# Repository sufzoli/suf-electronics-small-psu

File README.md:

# suf-electronics-small-psu
Collection of my small power supply circuits

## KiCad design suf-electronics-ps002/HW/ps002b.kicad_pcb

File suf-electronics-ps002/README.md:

suf-electronics-ps002
=====================

+/-12V 100mA USB Power Supply

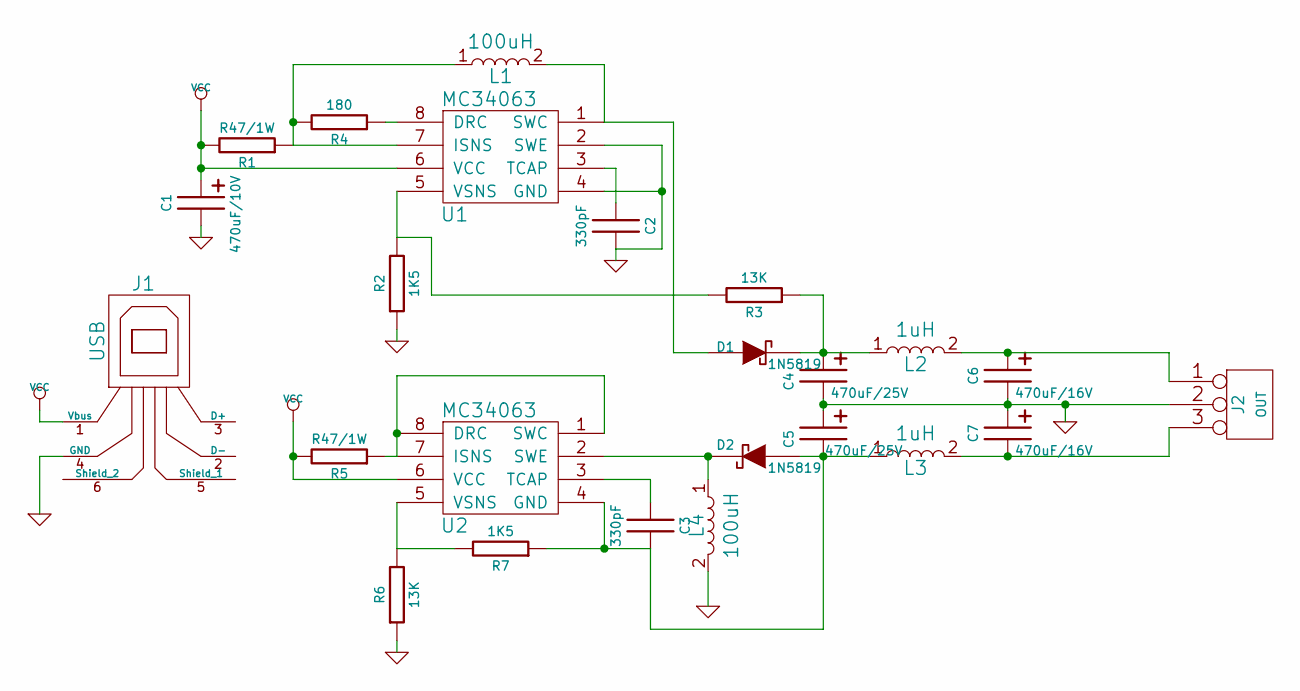
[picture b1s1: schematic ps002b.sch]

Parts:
C1: 470uF/10V; C2P_D4
C2, C3: 330pF; C1
C4, C5: 470uF/25V; C2P_D4
C6, C7: 470uF/16V; C2P_D4
D1, D2: 1N5819; D4
J1: USB; USB-B
J2: OUT; HDR-3
L1, L4: 100uH; L2_D3.5
L2, L3: 1uH; R5
R1, R5: R47/1W; R5
R2, R7: 1K5; R4
R3, R6: 13K; R4
R4: 180; R4
U1, U2: MC34063; DIP-8

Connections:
GND: C1.2, C2.1, C4.2, C5.1, C6.2, C7.1, J1.4 (GND), J2.2 (PM), L4.2, R2.2, R6.2, U1.2 (SWE), U1.4 (GND)
unnamed: C3.2, U2.3 (TCAP)
unnamed: R5.2, U2.1 (SWC), U2.7 (ISNS), U2.8 (DRC)
unnamed: R4.2, U1.8 (DRC)
unnamed: C3.1, C5.2, D2.1 (A), L3.1, R7.2, U2.4 (GND)
unnamed: R6.1, R7.1, U2.5 (VSNS)
unnamed: C6.1, J2.1, L2.2
unnamed: C7.2, J2.3, L3.2
unnamed: D2.2 (K), L4.1, U2.2 (SWE)
unnamed: C2.2, U1.3 (TCAP)
unnamed: R2.1, R3.1, U1.5 (VSNS)
unnamed: L1.1, R1.2, R4.1, U1.7 (ISNS)
unnamed: D1.1 (A), L1.2, U1.1 (SWC)
unnamed: C4.1, D1.2 (K), L2.1, R3.2
VCC: C1.1, J1.1 (Vbus), R1.1, R5.1, U1.6 (VCC), U2.6 (VCC)

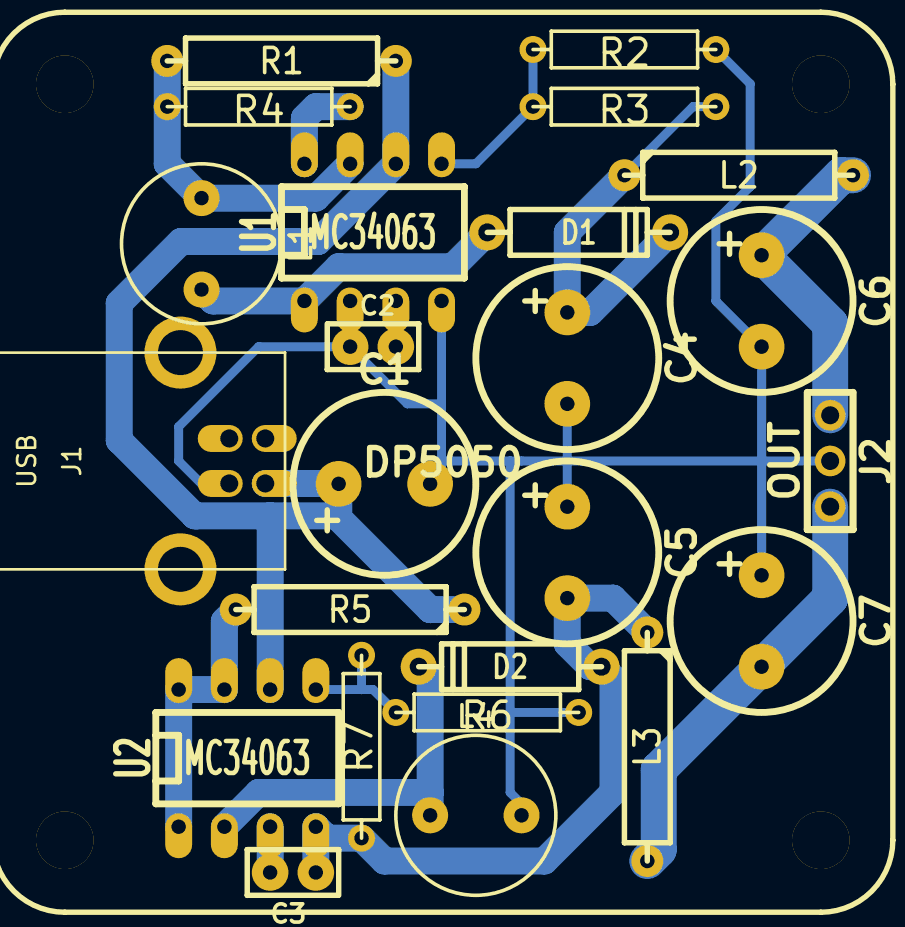
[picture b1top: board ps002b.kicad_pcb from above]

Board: 2 copper layers, 25 parts (0 on the bottom side), 15 nets.

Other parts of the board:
DP5050: DP5050

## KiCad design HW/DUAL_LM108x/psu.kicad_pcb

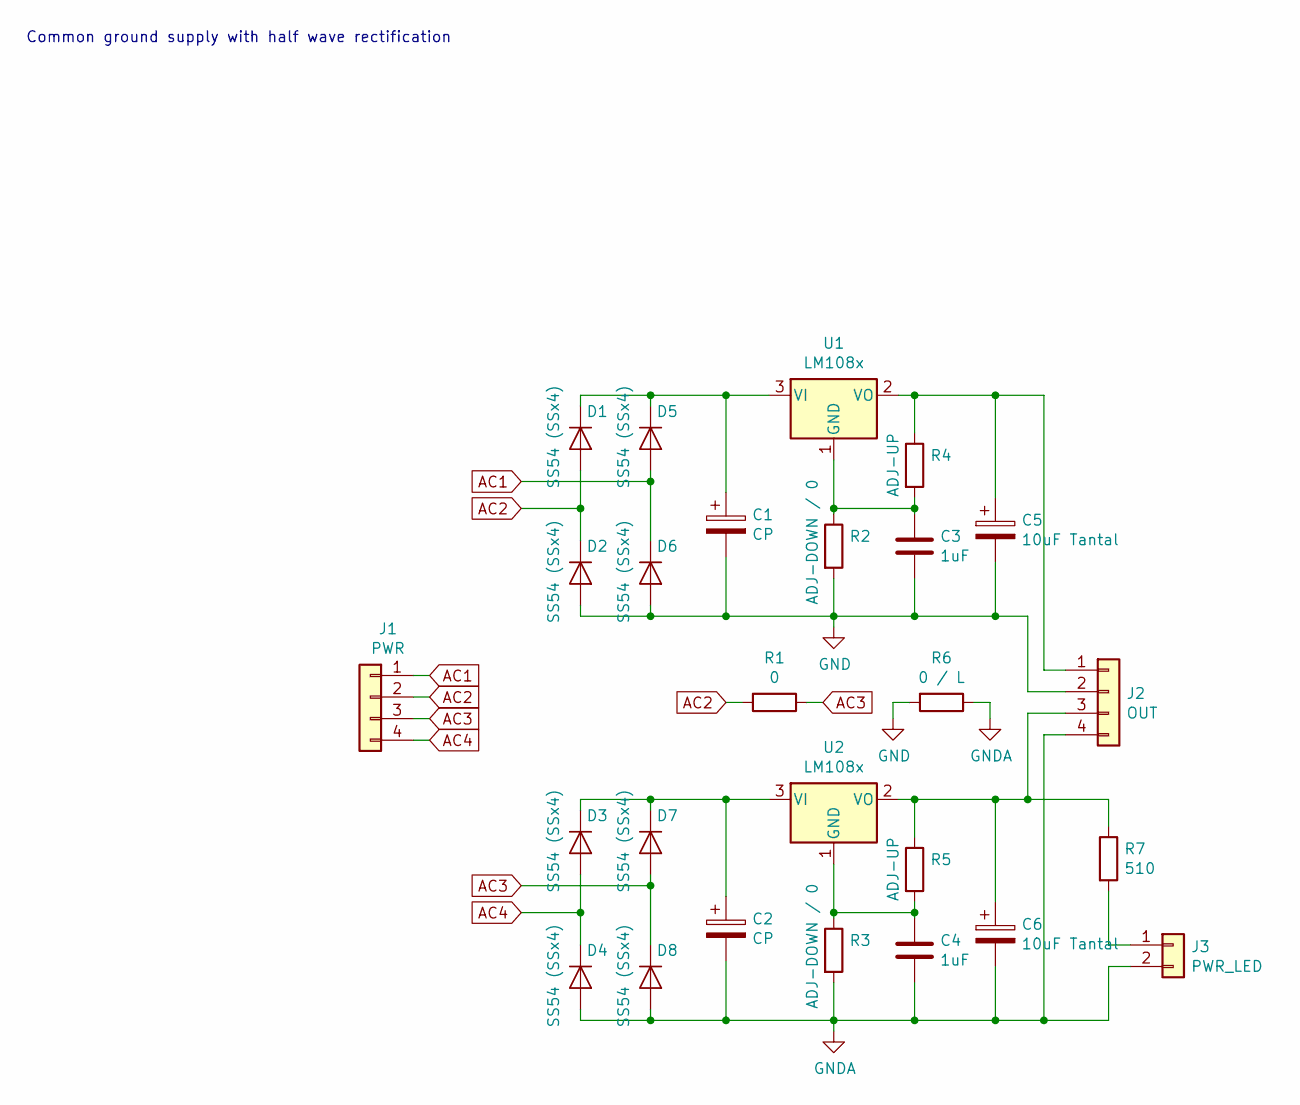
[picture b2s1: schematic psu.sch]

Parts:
C1, C2: CP; CP_Radial_D10.0mm_P5.00mm_P7.50mm
C3, C4: 1uF; C_0603_HandSoldering
C5, C6: 10uF Tantal; CP_Tantalum_Case-D_EIA-7343-31_Hand
D1, D2, D3, D4, D5, D6, D7, D8: SS54 (SSx4); D_SMB-SMC_Universal_Handsoldering
J1: PWR; PhoenixContact_MSTBA_2,5_4-G_1x04_P5.00mm_Horizontal
J2: OUT; PhoenixContact_MSTBA_2,5_4-G_1x04_P5.00mm_Horizontal
J3: PWR_LED; JST_EH_B02B-EH-A_02x2.50mm_Straight
R1: 0; R_2010_HandSoldering
R2, R3: ADJ-DOWN / 0; R_0603_HandSoldering
R4, R5: ADJ-UP; R_0603_HandSoldering
R6: 0 / L; R_2010_HandSoldering
R7: 510; R_0603_HandSoldering
U1, U2: LM108x; TO-220-3_Vertical

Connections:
AC1: D5.2 (A), D6.1 (K), J1.1
AC2: D1.2 (A), D2.1 (K), J1.2, R1.2
AC3: D7.2 (A), D8.1 (K), J1.3, R1.1
AC4: D3.2 (A), D4.1 (K), J1.4
GND: C1.2, C3.2, C5.2, D2.2 (A), D6.2 (A), J2.2, R2.2, R6.2
GNDA: C2.2, C4.2, C6.2, D4.2 (A), D8.2 (A), J2.4, J3.2, R3.2, R6.1
unnamed: C1.1, D1.1 (K), D5.1 (K), U1.3 (VI)
unnamed: C2.1, D3.1 (K), D7.1 (K), U2.3 (VI)
unnamed: C3.1, R2.1, R4.2, U1.1 (GND)
unnamed: C4.1, R3.1, R5.2, U2.1 (GND)
unnamed: C5.1, J2.1, R4.1, U1.2 (VO)
unnamed: C6.1, J2.3, R5.1, R7.1, U2.2 (VO)
unnamed: J3.1, R7.2

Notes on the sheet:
Common ground supply with half wave rectification

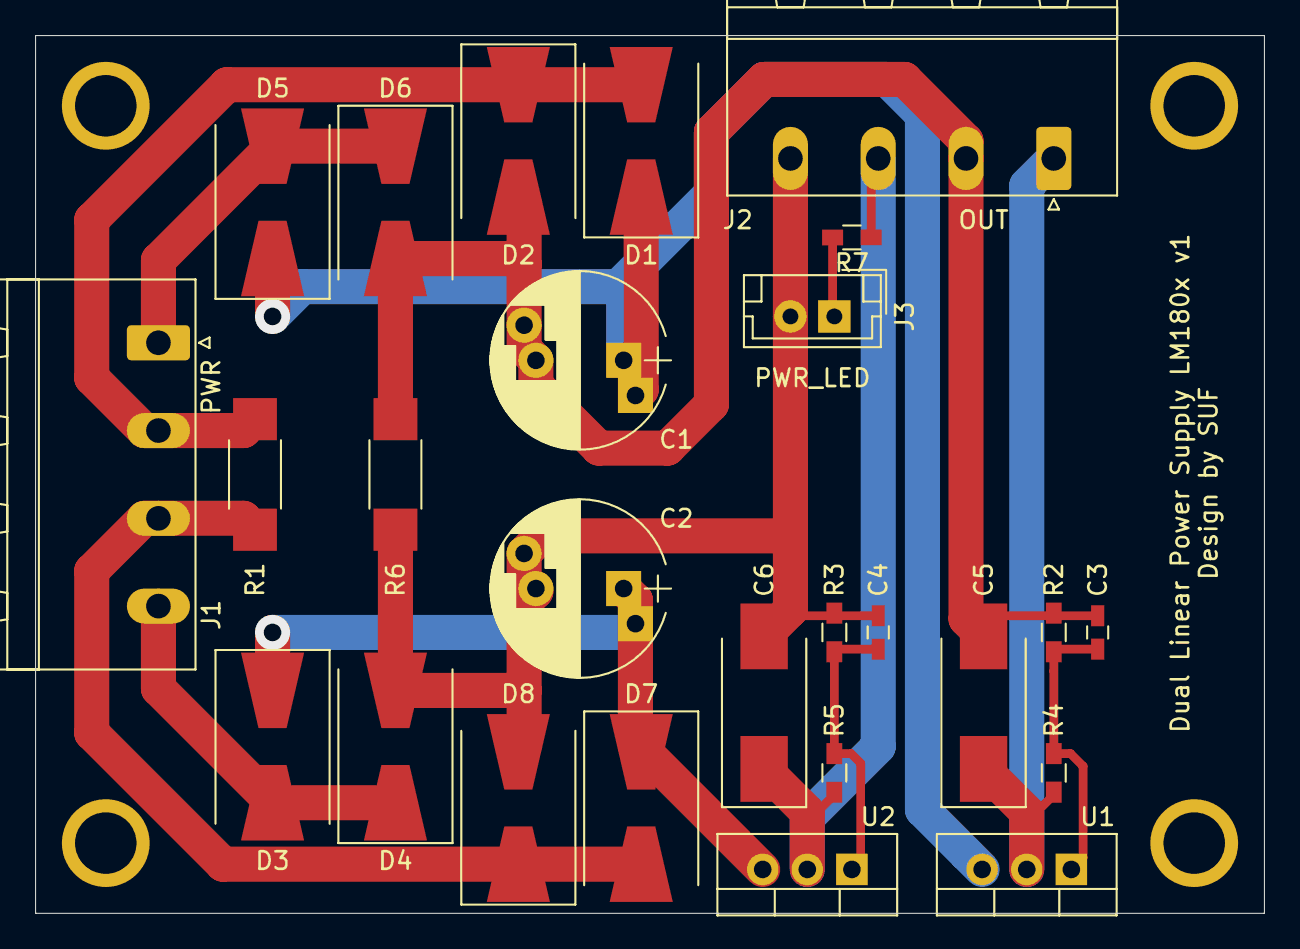
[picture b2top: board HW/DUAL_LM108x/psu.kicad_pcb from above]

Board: 2 copper layers, 70.0 x 50.0 mm, 30 parts (0 on the bottom side), 13 nets.

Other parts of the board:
MNT_HOLE_3.5S, MNT_HOLE_3.5S#2, MNT_HOLE_3.5S#3, MNT_HOLE_3.5S#4: Val**; MNT_HOLE_3.5S

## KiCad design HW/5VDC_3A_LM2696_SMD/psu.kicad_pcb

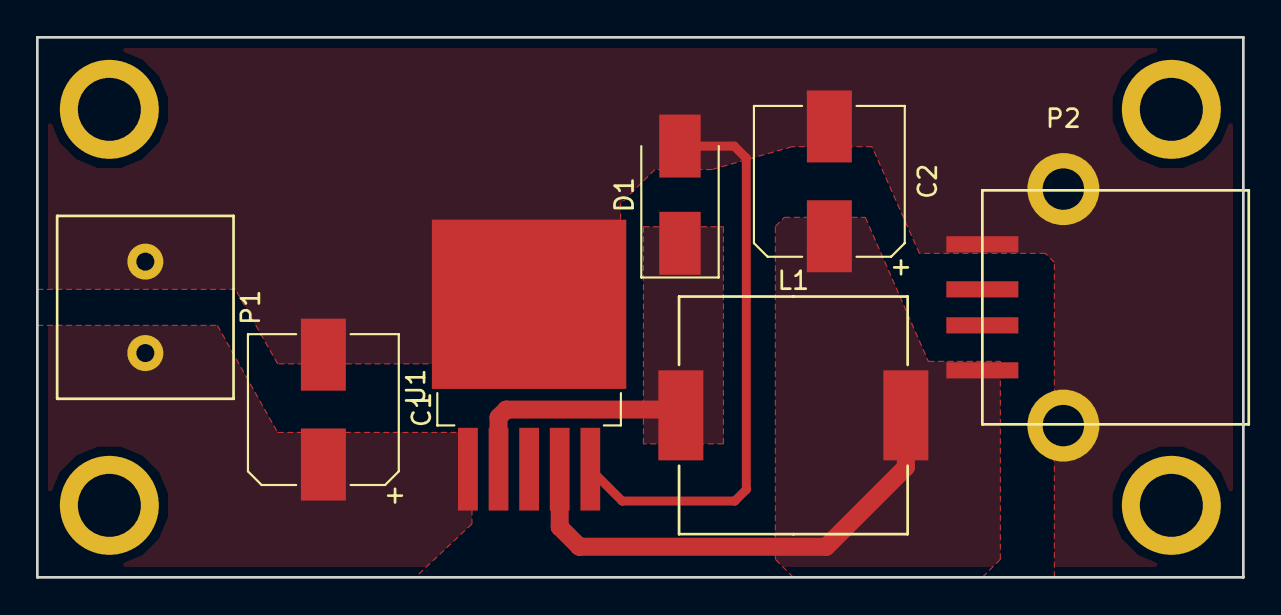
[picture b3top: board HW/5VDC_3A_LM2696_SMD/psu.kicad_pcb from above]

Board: 2 copper layers, 67.0 x 30.0 mm, 11 parts (0 on the bottom side), 4 nets.

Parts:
C1, C2: 470uF/16V; CP_Elec_8x10
D1: STPS340U; D_SMB_Handsoldering
L1: 33uH; Inductor_Wurth_HCM-1390
MNT_HOLE_3.5, MNT_HOLE_3.5#2, MNT_HOLE_3.5#3, MNT_HOLE_3.5#4: Val**; MNT_HOLE_3.5
P1: IN; Stelvio CLL5.08-2
P2: USB_A; USB-A_SMD
U1: TS2596-5.0; TO-263-5Lead

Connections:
GND: C1.2, C2.2, D1.2, P1.2, P2.4, U1.3, U1.5
unnamed: C1.1, P1.1, U1.1
unnamed: C2.1, L1.2, P2.1, U1.4
unnamed: D1.1, L1.1, U1.2

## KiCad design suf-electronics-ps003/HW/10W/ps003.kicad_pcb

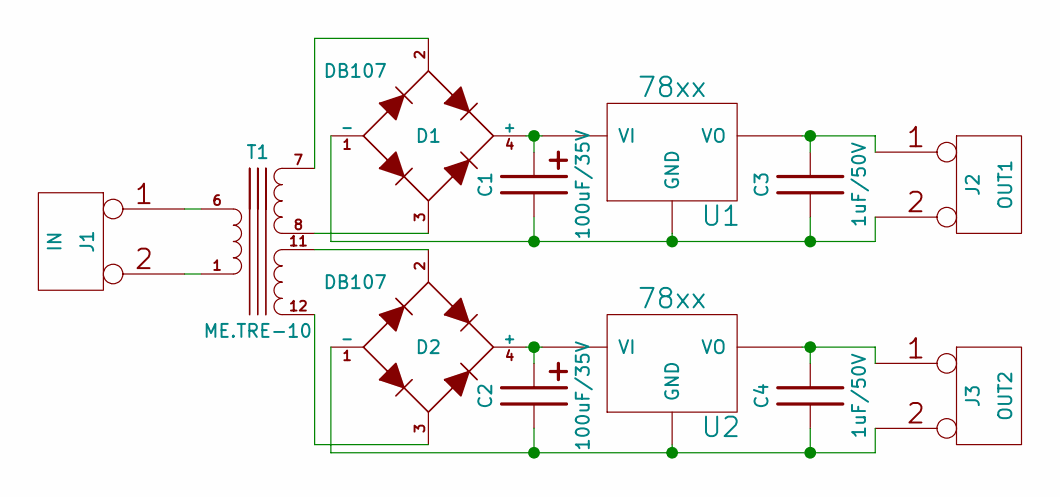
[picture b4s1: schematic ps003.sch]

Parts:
C1, C2: 100uF/35V; CP_Radial_D6.3mm_P2.50mm
C3, C4: 1uF/50V; C_Disc_D3.0mm_W1.6mm_P2.50mm
D1, D2: DB107; DB-4
J1: IN; CONN_NCW254-02S
J2: OUT1; CONN_NCW254-02S
J3: OUT2; CONN_NCW254-02S
T1: ME.TRE-10; TR_ME.TRE-10-2
U1, U2: 78xx; TO-220-3_Vertical

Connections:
unnamed: C1.1, D1.4 (+), U1.3 (VI)
unnamed: C1.2, C3.2, D1.1 (-), J2.2 (PM), U1.2 (GND)
unnamed: C2.1, D2.4 (+), U2.3 (VI)
unnamed: C2.2, C4.2, D2.1 (-), J3.2 (PM), U2.2 (GND)
unnamed: C3.1, J2.1, U1.1 (VO)
unnamed: C4.1, J3.1, U2.1 (VO)
unnamed: D1.2, T1.7
unnamed: D1.3, T1.8
unnamed: D2.2, T1.11
unnamed: D2.3, T1.12
unnamed: J1.1, T1.6
unnamed: J1.2 (PM), T1.1

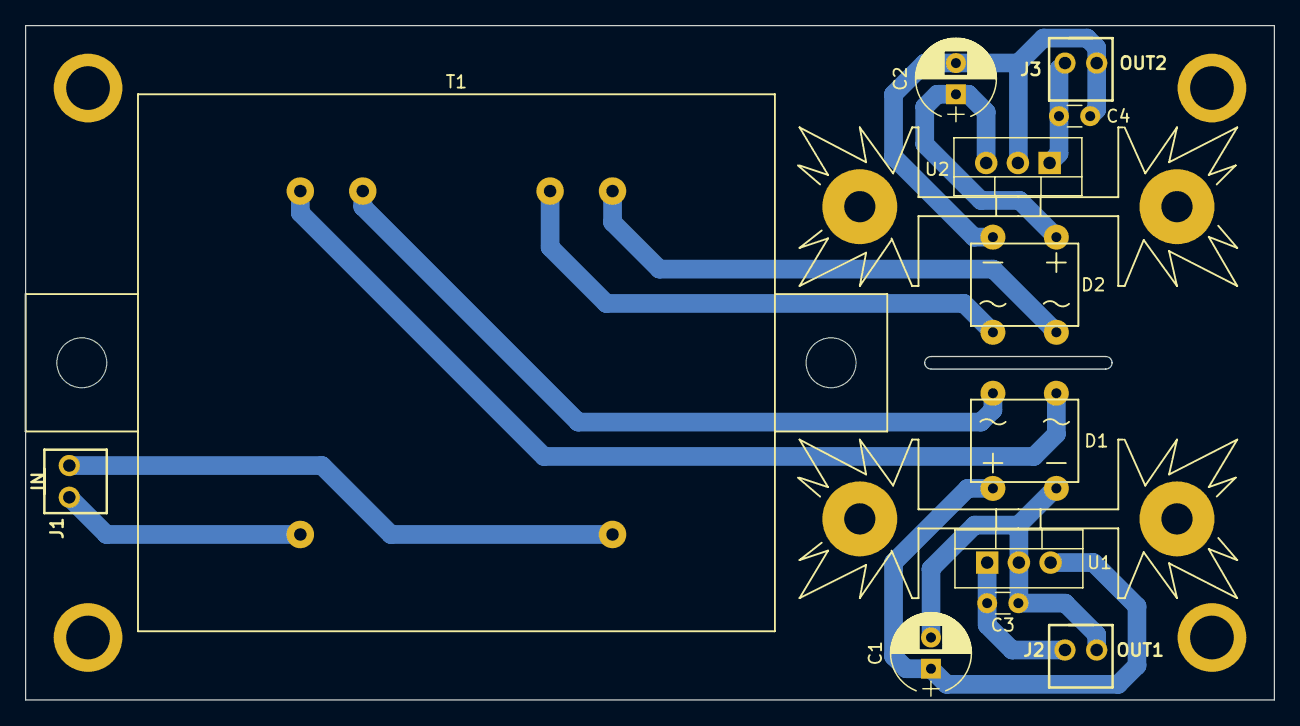
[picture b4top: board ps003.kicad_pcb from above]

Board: 2 copper layers, 100.0 x 54.0 mm, 16 parts (0 on the bottom side), 12 nets.

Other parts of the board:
MNT_HOLE_3.5, MNT_HOLE_3.5#2, MNT_HOLE_3.5#3, MNT_HOLE_3.5#4: Val**; MNT_HOLE_3.5

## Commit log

2021-03-20 Collect small PSUs to a single repo
